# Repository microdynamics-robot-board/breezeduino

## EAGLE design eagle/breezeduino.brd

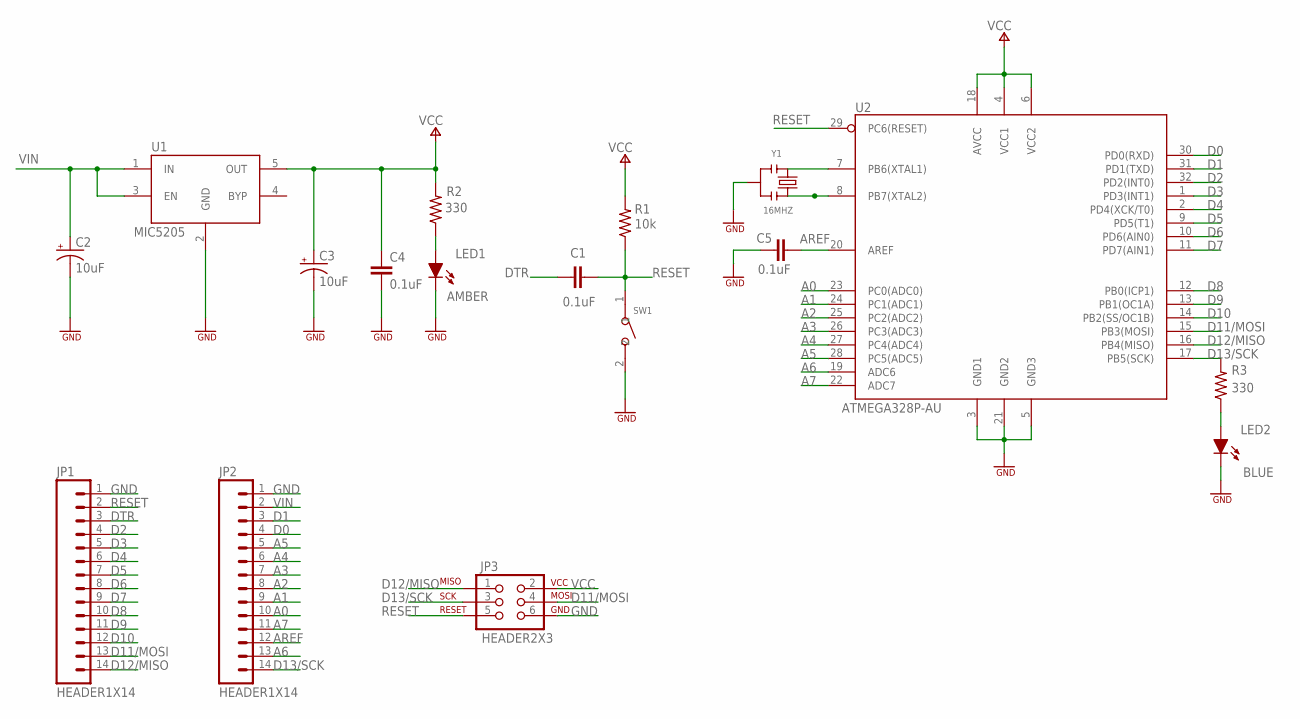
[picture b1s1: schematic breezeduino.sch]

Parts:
C1, C4, C5: 0.1uF; SMD0603
C2, C3: 10uF; EIA3216
JP1, JP2: HEADER1X14; 1X14
JP3: HEADER2X3; 2X3
LED1: AMBER; LED_0603
LED2: BLUE; LED_0805
R1: 10k; SMD0603
R2, R3: 330; SMD0603
SW1: SMD-BUTTON(2P-3.0X2.5X1.2+0.4MM)-B3U-1000P-2P-SMD; SW2-2.6-3.0X2.5X1.2+0.4MM
U1: MIC5205; SOT23-5
U2: ATMEGA328P-AU; TQFP32
Y1: 16MHZ; X3-SMD-3.6X1.3X0.8MM

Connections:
A0: JP2.10, U2.23 (PC0(ADC0))
A1: JP2.9, U2.24 (PC1(ADC1))
A2: JP2.8, U2.25 (PC2(ADC2))
A3: JP2.7, U2.26 (PC3(ADC3))
A4: JP2.6, U2.27 (PC4(ADC4))
A5: JP2.5, U2.28 (PC5(ADC5))
A6: JP2.13, U2.19 (ADC6)
A7: JP2.11, U2.22 (ADC7)
AREF: C5.1, JP2.12, U2.20 (AREF)
D0: JP2.4, U2.30 (PD0(RXD))
D1: JP2.3, U2.31 (PD1(TXD))
D2: JP1.4, U2.32 (PD2(INT0))
D3: JP1.5, U2.1 (PD3(INT1))
D4: JP1.6, U2.2 (PD4(XCK/T0))
D5: JP1.7, U2.9 (PD5(T1))
D6: JP1.8, U2.10 (PD6(AIN0))
D7: JP1.9, U2.11 (PD7(AIN1))
D8: JP1.10, U2.12 (PB0(ICP1))
D9: JP1.11, U2.13 (PB1(OC1A))
D10: JP1.12, U2.14 (PB2(SS/OC1B))
D11/MOSI: JP1.13, JP3.4, U2.15 (PB3(MOSI))
D12/MISO: JP1.14, JP3.1, U2.16 (PB4(MISO))
D13/SCK: JP2.14, JP3.3, R3.2, U2.17 (PB5(SCK))
DTR: C1.1, JP1.3
GND: C2.C (-), C3.C (-), C4.2, C5.2, JP1.1, JP2.1, JP3.6, LED1.C, LED2.C, SW1.2, U1.2 (GND), U2.3 (GND1), U2.5 (GND3), U2.21 (GND2), Y1.2
unnamed: U2.7 (PB6(XTAL1)), Y1.1
unnamed: U2.8 (PB7(XTAL2)), Y1.3
unnamed: LED1.A, R2.1
unnamed: LED2.A, R3.1
RESET: C1.2, JP1.2, JP3.5, R1.1, SW1.1, U2.29 (PC6(RESET))
VCC: C3.A (+), C4.1, JP3.2, R1.2, R2.2, U1.5 (OUT), U2.4 (VCC1), U2.6 (VCC2), U2.18 (AVCC)
VIN: C2.A (+), JP2.2, U1.1 (IN), U1.3 (EN)

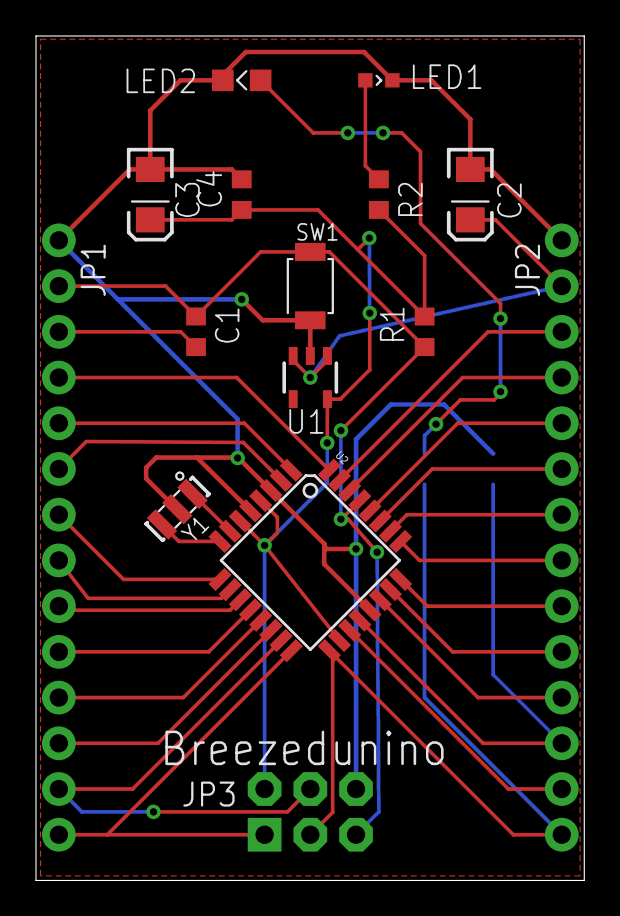
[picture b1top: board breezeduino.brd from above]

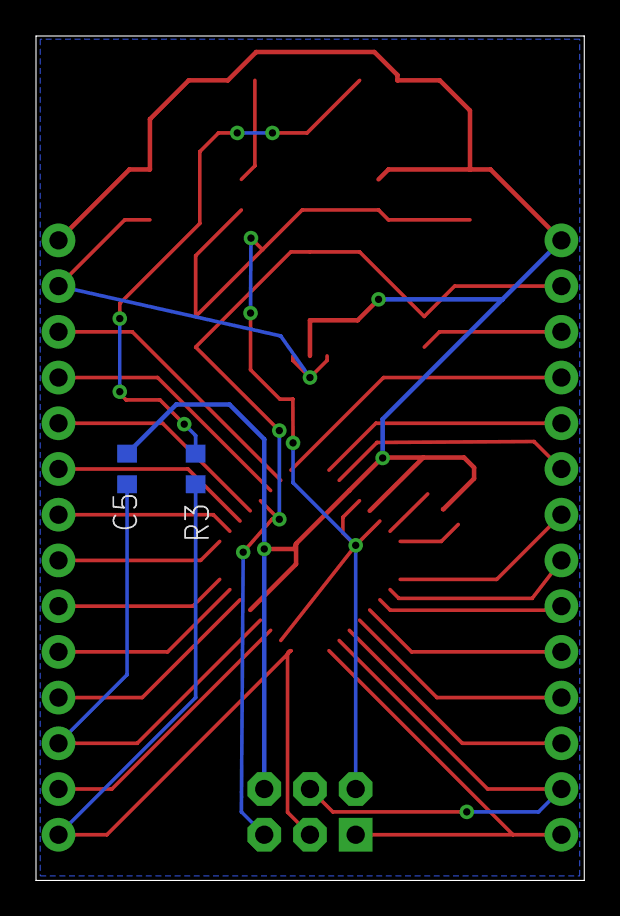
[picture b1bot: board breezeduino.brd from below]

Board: 2 copper layers, 30.5 x 46.9 mm, 17 parts (2 on the bottom side), 32 nets.

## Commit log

2017-12-16 Add gitignore file
2017-12-16 Modify gitignore file
2017-12-16 Fix a bug in gitignore file
2017-12-16 Add breezeduino eagle's file
